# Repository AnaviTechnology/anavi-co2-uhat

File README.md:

# ANAVI CO2 uHAT

ANAVI CO2 uHAT is an open source hardware Raspberry Pi uHAT (add-on board) for rapid prototyping of Internet of Things (IoT) powered by free and open source software. It features:

* Red and green indication LEDs
* Slots for MH-Z19B CO2 and temperature sensor
* Slot of mini OLED I2C display
* Slots for up to 3 plug and play I2C sensors for temperature, barometric pressure, humidity and light

# Safety Information

## English

### Warnings

* This product shall only be connected to a compatible Raspberry Pi.

### Instructions for safe use

* Do not expose this product to water or moisture, and do not place it on a conductive surface whilst in operation.
* Do not expose this product to heat from any source; it is designed for reliable operation at normal room temperatures.
* Take care while handling this product to avoid mechanical or electrical damage to the printed circuit board and connectors.
* Avoid handling this product while it is powered. Only handle by the edges to minimize the risk of electrostatic discharge damage.

## Deutsch

### Achtung

* Dieses Produkt darf nur mit einem kompatiblen Raspberry Pi verbunden werden.

### Anweisungen für die sichere Verwendung

* Setzen Sie dieses Produkt nicht Wasser oder Feuchtigkeit aus und stellen Sie es während des Betriebs nicht auf eine leitfähige Oberfläche.
* Setzen Sie dieses Produkt keiner Wärmequelle aus. Es ist für einen zuverlässigen Betrieb bei normalen Raumtemperaturen ausgelegt.
* Seien Sie vorsichtig beim Umgang mit diesem Produkt, um mechanische oder elektrische Schäden an der Leiterplatte und den Anschlüssen zu vermeiden.
* Vermeiden Sie die Handhabung dieses Produkts während der Stromversorgung. Produkt nur an den Rändern anfassen, um das Risiko von elektrostatischen Entladungsschäden zu minimieren.

# License

The project is released under the [Creative Commons Attribution-ShareAlike 4.0 International (CC BY-SA 4.0)](https://creativecommons.org/licenses/by-sa/4.0/).

Note: This is a human-readable summary of (and not a substitute for) the [license](https://creativecommons.org/licenses/by-sa/4.0/legalcode).

You are free to:

Share — copy and redistribute the material in any medium or format Adapt — remix, transform, and build upon the material for any purpose, even commercially. The licensor cannot revoke these freedoms as long as you follow the license terms. Under the following terms:

Attribution — You must give appropriate credit, provide a link to the license, and indicate if changes were made. You may do so in any reasonable manner, but not in any way that suggests the licensor endorses you or your use. ShareAlike — If you remix, transform, or build upon the material, you must distribute your contributions under the same license as the original. No additional restrictions — You may not apply legal terms or technological measures that legally restrict others from doing anything the license permits. Notices:

You do not have to comply with the license for elements of the material in the public domain or where your use is permitted by an applicable exception or limitation. No warranties are given. The license may not give you all of the permissions necessary for your intended use. For example, other rights such as publicity, privacy, or moral rights may limit how you use the material.

You will have to provide a link to the original creator of the project http://www.anavi.technology on any documentation or website.

Credit can be attributed through a link to the creator website: http://www.anavi.technology

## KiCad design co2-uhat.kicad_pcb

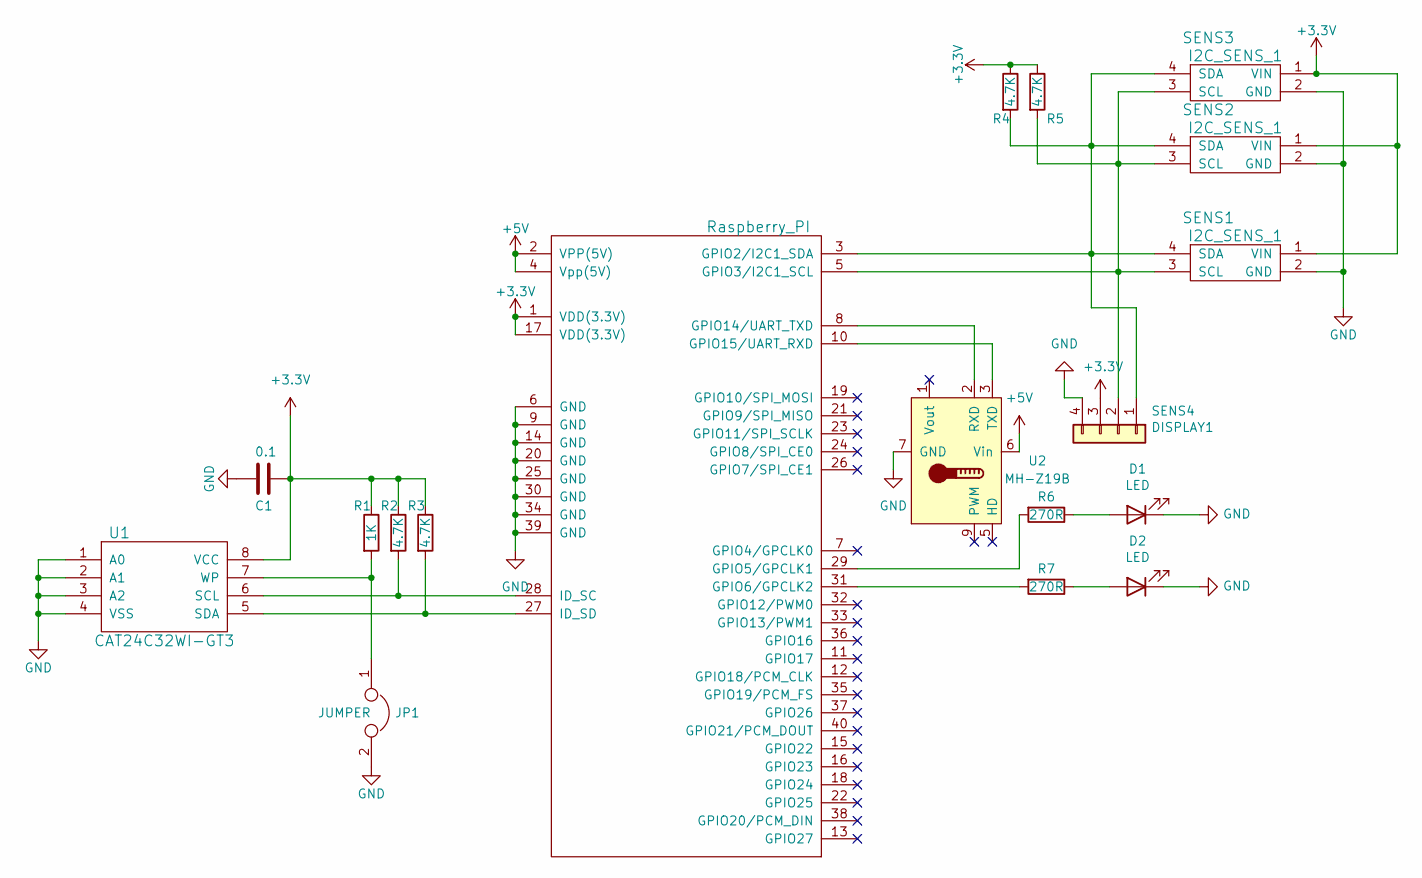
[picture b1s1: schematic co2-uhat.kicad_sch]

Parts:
C1: 0.1; C_0603_HandSoldering
D1, D2: LED; LED_1206_3216Metric
JP1: JUMPER; Pin_Header_Straight_1x02
R1: 1K; R_0603_HandSoldering
R2, R3, R4, R5: 4.7K; R_0603_HandSoldering
R6, R7: 270R; R_0603_HandSoldering
RASP_CONN1: Raspberry_PI; Pin_Header_Straight_2x20
SENS1, SENS2, SENS3: I2C_SENS_1; Pin_Header_Straight_1x04
SENS4: DISPLAY1; Pin_Header_Straight_1x04
U1: CAT24C32WI-GT3; DIP-8_W7.62mm
U2: MH-Z19B; Winsen_MH-Z19B

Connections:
+3V3: C1.1, R1.1, R2.1, R3.1, R4.1, R5.1, RASP_CONN1.1 (VDD(3.3V)), RASP_CONN1.17 (VDD(3.3V)), SENS1.1 (VIN), SENS2.1 (VIN), SENS3.1 (VIN), SENS4.3, U1.8 (VCC); also elsewhere on the board
+5V: RASP_CONN1.2 (VPP(5V)), RASP_CONN1.4 (Vpp(5V)), U2.6 (Vin)
GND: C1.2, D1.1 (K), D2.1 (K), JP1.2, RASP_CONN1.6 (GND), RASP_CONN1.9 (GND), RASP_CONN1.14 (GND), RASP_CONN1.20 (GND), RASP_CONN1.25 (GND), RASP_CONN1.30 (GND), RASP_CONN1.34 (GND), RASP_CONN1.39 (GND), SENS1.2 (GND), SENS2.2 (GND), SENS3.2 (GND), SENS4.4, U1.1 (A0), U1.2 (A1), U1.3 (A2), U1.4 (VSS), U2.7 (GND); also elsewhere on the board
unnamed: D1.2 (A), R6.1
unnamed: D2.2 (A), R7.1
unnamed: JP1.1, R1.2, U1.7 (WP)
unnamed: R2.2, RASP_CONN1.28 (ID_SC), U1.6 (SCL)
unnamed: R3.2, RASP_CONN1.27 (ID_SD), U1.5 (SDA)
unnamed 8: R4.2, RASP_CONN1.3 (GPIO2/I2C1_SDA), SENS1.4 (SDA), SENS2.4 (SDA), SENS3.4 (SDA), SENS4.1; also elsewhere on the board
unnamed 9: R5.2, RASP_CONN1.5 (GPIO3/I2C1_SCL), SENS1.3 (SCL), SENS2.3 (SCL), SENS3.3 (SCL), SENS4.2; also elsewhere on the board
unnamed: R6.2, RASP_CONN1.29 (GPIO5/GPCLK1)
unnamed: R7.2, RASP_CONN1.31 (GPIO6/GPCLK2)
unnamed: RASP_CONN1.8 (GPIO14/UART_TXD), U2.2 (RXD)
unnamed: RASP_CONN1.10 (GPIO15/UART_RXD), U2.3 (TXD)

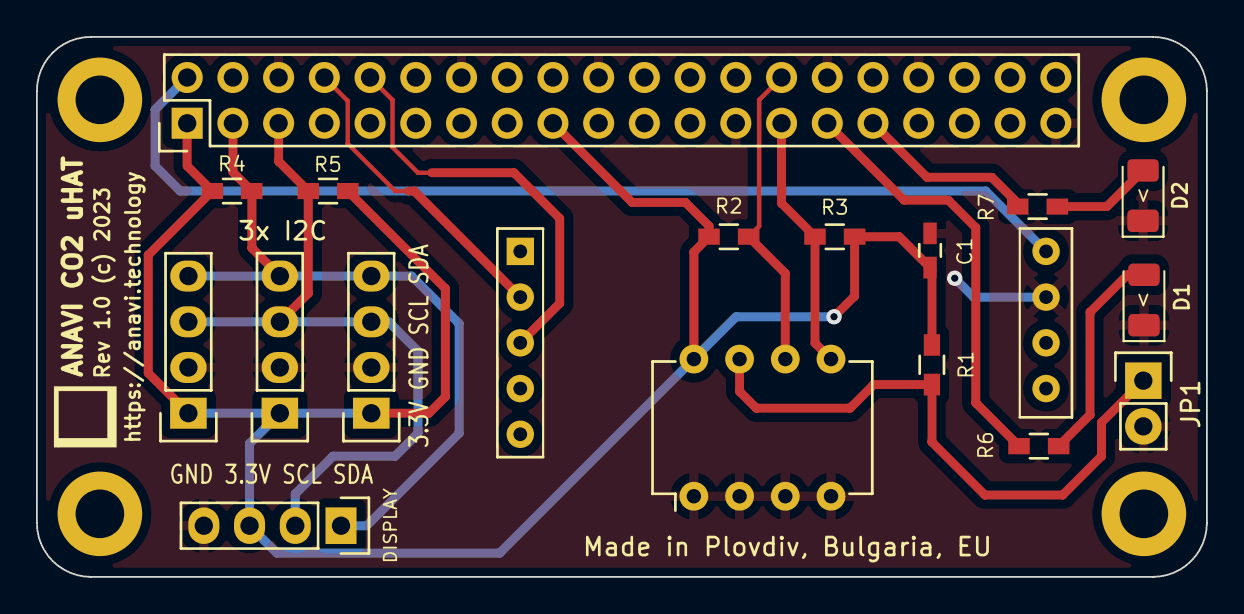
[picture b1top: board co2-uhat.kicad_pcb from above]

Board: 2 copper layers, 65.0 x 30.0 mm, 22 parts (0 on the bottom side), 14 nets.

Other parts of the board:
DISPLAY: DISPLAY1; Pin_Header_Straight_1x04
REF1, REF2, REF3, REF4: MountingHole_2.7mm_M2.5_DIN965_Pad

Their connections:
+3V3: DISPLAY.3; also elsewhere on the board
GND: DISPLAY.4; also elsewhere on the board
unnamed 8: DISPLAY.1; also elsewhere on the board
unnamed 9: DISPLAY.2; also elsewhere on the board

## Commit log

2023-08-07 anavi-co2-uhat: Initial commit
2023-08-07 co2-uhat.kicad_pcb: Add traces
    Add traces to the PCB.
2023-08-08 .gitignore: Ignore co2-uhat-backups
2023-08-08 co2-uhat.kicad_pcb: Move display
    Move display and add labels.
2023-08-08 .gitignore: Ignore all backups
2023-08-18 co2-uhat.kicad_pcb: Fab layer
    Add and adjust values on the front fabrication layer.
2023-08-28 co2-uhat.kicad_pcb: Adjust labels
    Adjust labels on the front silkscreen and fabrication layer.

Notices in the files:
co2-uhat.kicad_pcb:
Rev 1.0 (c) 2023
